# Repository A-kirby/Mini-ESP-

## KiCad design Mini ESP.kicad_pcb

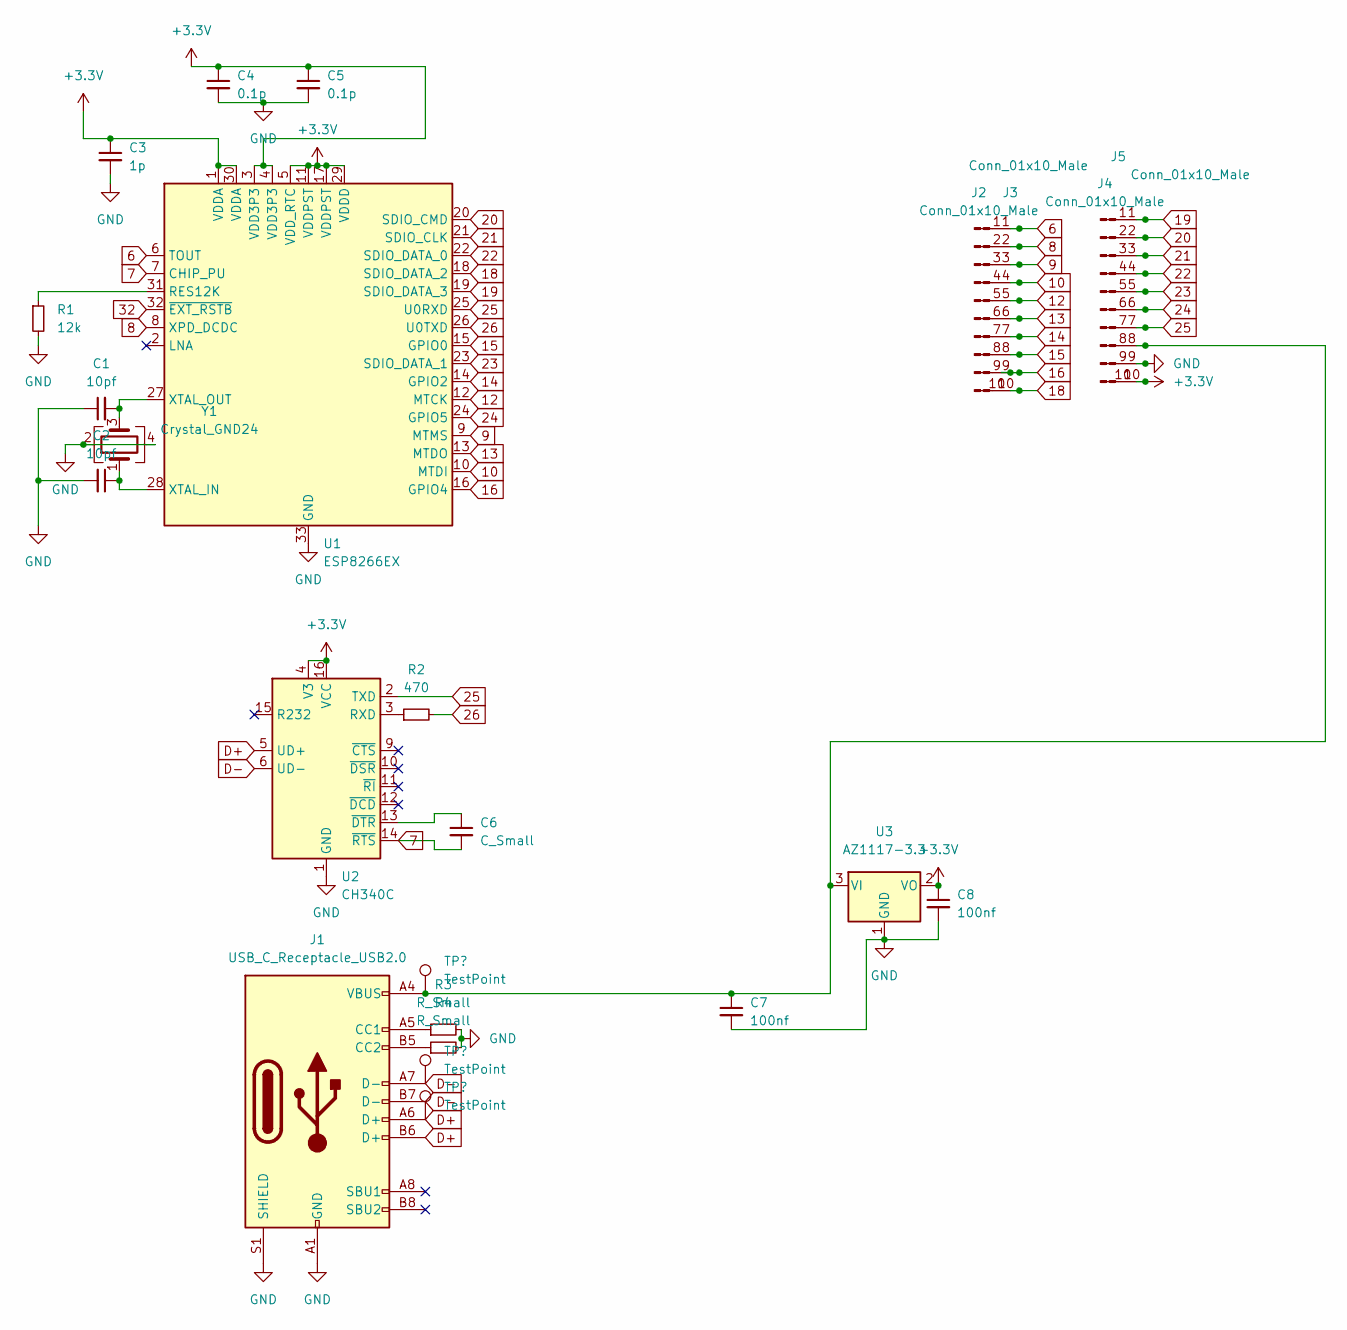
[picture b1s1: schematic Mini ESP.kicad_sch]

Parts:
C1, C2: 10pf
C3: 1p
C4, C5: 0.1p
C6: C_Small
C7, C8: 100nf
J1: USB_C_Receptacle_USB2.0; USB_C_Receptacle_HRO_TYPE-C-31-M-12
J2, J3, J4, J5: Conn_01x10_Male
R1: 12k
R2: 470
R3, R4: R_Small
U1: ESP8266EX; QFN-32-1EP_5x5mm_P0.5mm_EP3.45x3.45mm
U2: CH340C; SOIC-16_3.9x9.9mm_P1.27mm
U3: AZ1117-3.3
Y1: Crystal_GND24

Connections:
6: J2.1, J3.1, U1.6 (TOUT)
7: C6.2, U1.7 (CHIP_PU), U2.14 (~RTS)
8: J2.2, J3.2, U1.8 (XPD_DCDC)
9: J2.3, J3.3, U1.9 (MTMS)
10: J2.4, J3.4, U1.10 (MTDI)
12: J2.5, J3.5, U1.12 (MTCK)
13: J2.6, J3.6, U1.13 (MTDO)
14: J2.7, J3.7, U1.14 (GPIO2)
15: J2.8, J3.8, U1.15 (GPIO0)
16: J2.9, J3.9, U1.16 (GPIO4)
18: J2.10, J3.10, U1.18 (SDIO_DATA_2)
19: J4.1, J5.1, U1.19 (SDIO_DATA_3)
20: J4.2, J5.2, U1.20 (SDIO_CMD)
21: J4.3, J5.3, U1.21 (SDIO_CLK)
22: J4.4, J5.4, U1.22 (SDIO_DATA_0)
23: J4.5, J5.5, U1.23 (SDIO_DATA_1)
24: J4.6, J5.6, U1.24 (GPIO5)
25: J4.7, J5.7, U1.25 (U0RXD), U2.2 (TXD)
26: R2.2, U1.26 (U0TXD)
32: U1.32 (~EXT_RSTB)
+3.3V: C3.1, C4.1, C5.1, C8.1, J4.10, J5.10, U1.1 (VDDA), U1.3 (VDD3P3), U1.4 (VDD3P3), U1.5 (VDD_RTC), U1.11 (VDDPST), U1.17 (VDDPST), U1.29 (VDDD), U1.30 (VDDA), U2.4 (V3), U2.16 (VCC), U3.2 (VO)
D+: J1.A6 (D+), J1.B6 (D+), U2.5 (UD+); also elsewhere on the board
D-: J1.A7 (D-), J1.B7 (D-), U2.6 (UD-); also elsewhere on the board
GND: C1.1, C2.2, C3.2, C4.2, C5.2, C7.2, C8.2, J1.A1 (GND), J1.A12 (GND), J1.B1 (GND), J1.B12 (GND), J1.S1 (SHIELD), J4.9, J5.9, R1.2, R3.2, R4.2, U1.33 (GND), U2.1 (GND), U3.1 (GND), Y1.2, Y1.4
unnamed: C1.2, U1.27 (XTAL_OUT), Y1.3
unnamed: C2.1, U1.28 (XTAL_IN), Y1.1
unnamed: C6.1, U2.13 (~DTR)
unnamed 27: C7.1, J1.A4 (VBUS), J1.A9 (VBUS), J1.B4 (VBUS), J1.B9 (VBUS), J4.8, J5.8, U3.3 (VI); also elsewhere on the board
unnamed: J1.A5 (CC1), R3.1
unnamed: J1.B5 (CC2), R4.1
unnamed: R1.1, U1.31 (RES12K)
unnamed: R2.1, U2.3 (RXD)

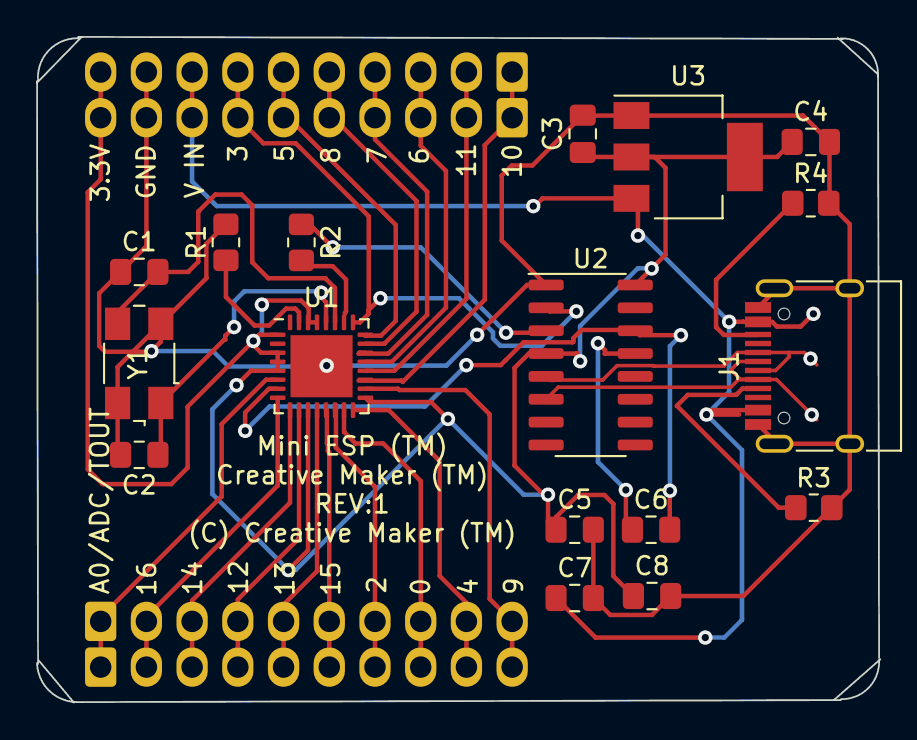
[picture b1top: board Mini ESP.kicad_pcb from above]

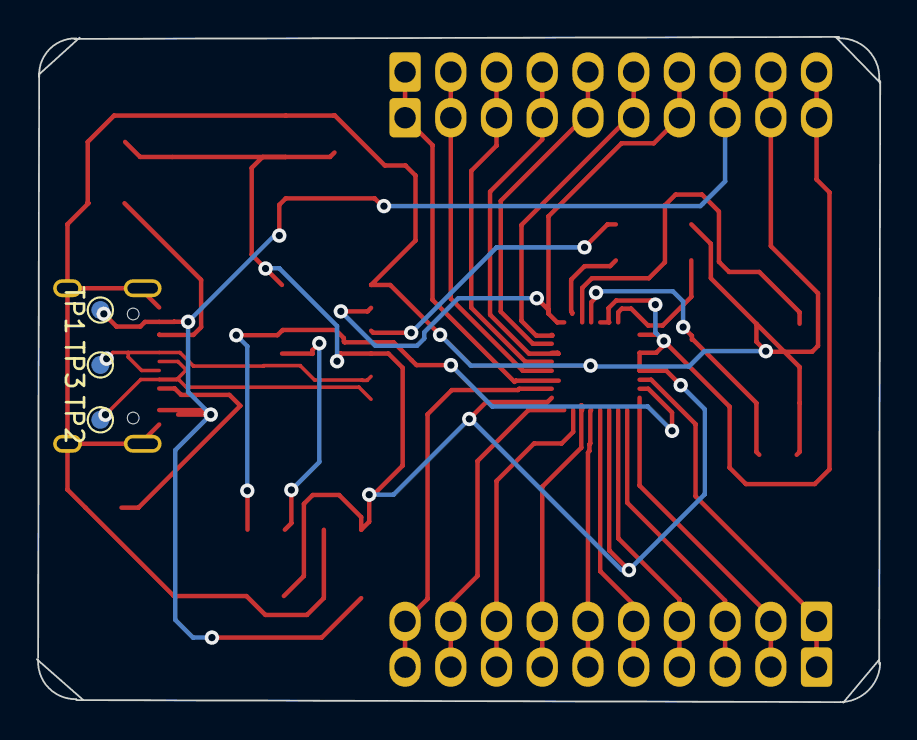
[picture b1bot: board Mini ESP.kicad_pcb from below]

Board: 2 copper layers, 46.9 x 37.0 mm, 24 parts (3 on the bottom side), 31 nets.

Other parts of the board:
TP1, TP2, TP3: TestPoint; TestPoint_Pad_D1.0mm

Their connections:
D+: TP3.1; also elsewhere on the board
D-: TP2.1; also elsewhere on the board
unnamed 27: TP1.1; also elsewhere on the board
